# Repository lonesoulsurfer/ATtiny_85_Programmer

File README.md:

# ATtiny 85 Programmer

*Parts list can be found in the Instructables link below*

Make your own ATtiny 85 programmer using an Arduino Nano and a custom made PCB!

I've been building a few projects of late that use a ATtiny 85 microcontrollers and wanted to create a specifically designed programmer to make the job easier.

If you are an old hand with programming ATtiny 85's or a total novice and want to learn, then this bit of kit is essential. Once you have the hardware, programming the ATtiny becomes quite simple. 

Check out the video of the build and how to program the ATTiny 85 here:https://www.youtube.com/watch?v=726uLVw5450&feature=youtu.be

I've also done a step by step guide on Instructables which you can find here: https://www.instructables.com/Programmer-for-ATtiny-85/

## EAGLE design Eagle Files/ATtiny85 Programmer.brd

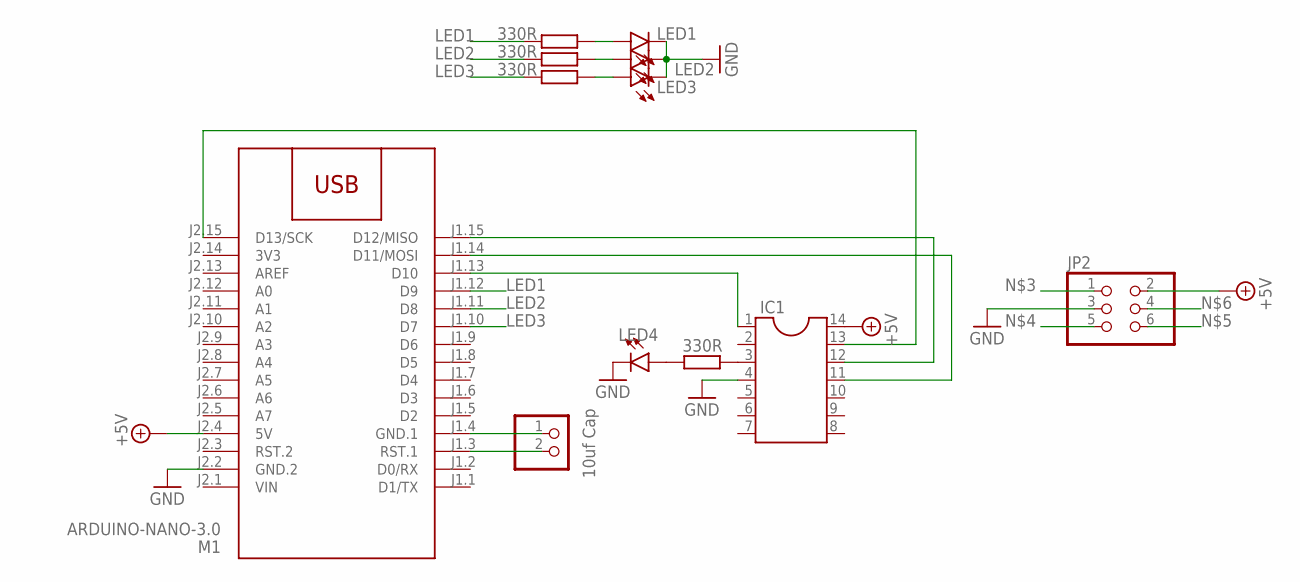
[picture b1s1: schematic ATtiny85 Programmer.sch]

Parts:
IC1: DIL14
JP1: 10uf Cap; 1X02
JP2: PINHD-2X3; 2X03
LED1, LED2, LED3, LED4: LED3MM
M1: ARDUINO-NANO-3.0
R1, R2, R3, R4: 330R; 0207/10

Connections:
3V3: M1.J2.14 (3V3)
+5V: IC1.14, JP2.2, M1.J2.4 (5V)
GND: IC1.4, JP2.3, LED1.K (C), LED2.K (C), LED3.K (C), LED4.K (C), M1.J2.2 (GND.2)
LED1: M1.J1.12 (D9), R4.1
LED2: M1.J1.11 (D8), R1.1
LED3: M1.J1.10 (D7), R2.1
unnamed: JP1.2, M1.J1.3 (RST.1)
unnamed: JP1.1, M1.J1.4 (GND.1)
unnamed: IC1.1, JP2.1, M1.J1.13 (D10)
unnamed: IC1.11, JP2.5, M1.J1.14 (D11/MOSI)
unnamed: IC1.12, JP2.6, M1.J1.15 (D12/MISO)
unnamed: IC1.13, JP2.4, M1.J2.15 (D13/SCK)
unnamed: IC1.3, R3.2
unnamed: LED1.A, R4.2
unnamed: LED2.A, R1.2
unnamed: LED3.A, R2.2
unnamed: LED4.A, R3.1
VIN: M1.J2.1 (VIN)

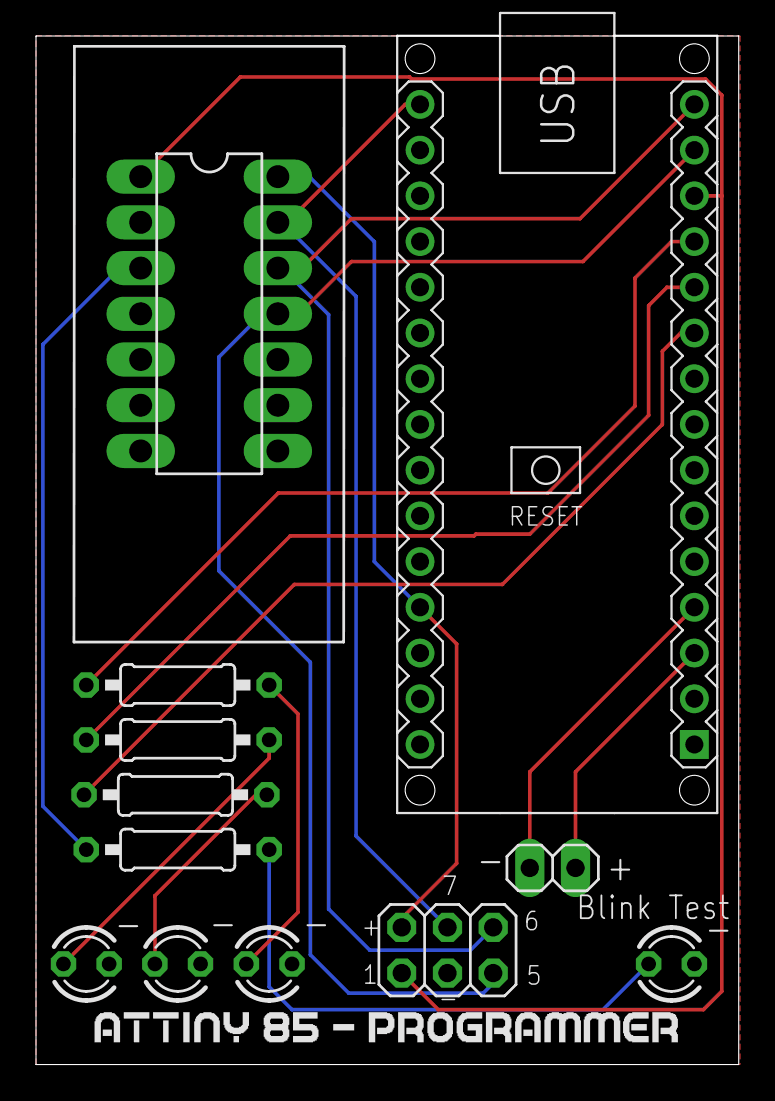
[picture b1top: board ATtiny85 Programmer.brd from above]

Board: 2 copper layers, 39.0 x 57.1 mm, 12 parts (0 on the bottom side), 16 nets.

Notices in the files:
parts and their libraries:
diy-modules: Released under the Creative Commons Attribution 4.0 International License: http://creativecommons.org/licenses/by/4.0
